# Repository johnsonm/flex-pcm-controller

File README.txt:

This is a low-current low-DC-voltage 2.5cm by 5cm PCM controller based
on a 555 timer.  It is built in KiCad.  The license, which applies to
all unique content (not inherited components) is in the LICENSE.txt
file.  Instructions for some potential modifications and use are in
the schematic.

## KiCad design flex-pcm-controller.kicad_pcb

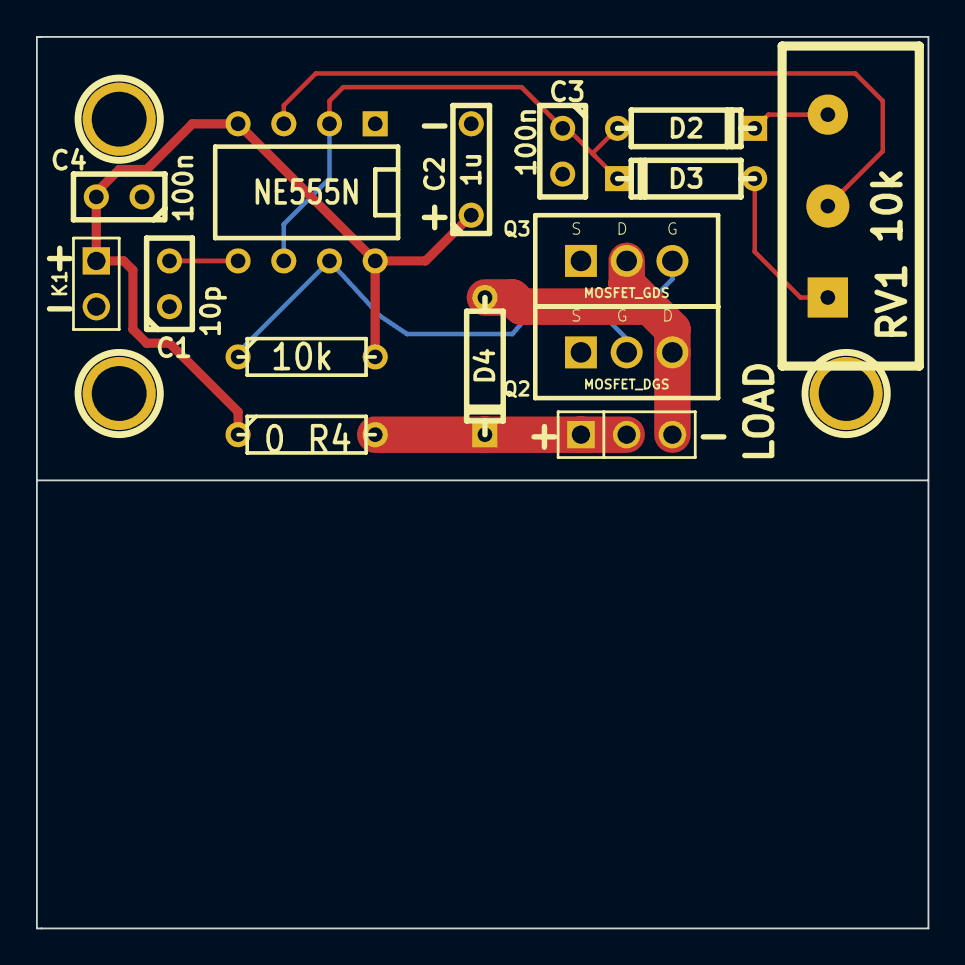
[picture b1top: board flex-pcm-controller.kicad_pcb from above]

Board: 2 copper layers, 49.5 x 49.5 mm, 18 parts (0 on the bottom side), 10 nets.

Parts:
1PIN, 1PIN#2, 1PIN#3: P***; 1pin
C1: 10p; C1
C2: 1u; C2
C3, C4: 100n; C1
D2, D3, D4: DIODESCH; D3
K1: POWER; PIN_ARRAY_2X1
K2: LOAD; PIN_ARRAY_3X1
Q2: MOSFET_DGS; TO220DGS
Q3: MOSFET_GDS; TO220GDS
R2: 10k; R3
R4: 0; R3
RV1: 10k; POTA_Fav
U1: NE555N; DIP-8__300

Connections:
/SIG: Q2.G, Q3.G, R2.1, U1.7
/Vload+: D4.2, K2.1, K2.2, R4.2
/Vload-: D4.1, K2.3, Q2.D, Q3.D
GND: C1.1, C2.2, C3.2, C4.1, K1.2, Q2.S, Q3.S, U1.1
unnamed: D2.2, RV1.3
unnamed: RV1.2, U1.3
unnamed: D3.1, RV1.1
unnamed: C1.2, U1.5
unnamed: C3.1, D2.1, D3.2, U1.2, U1.6
VCC: C2.1, C4.2, K1.1, R2.2, R4.1, U1.4, U1.8

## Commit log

2014-09-16 Initial version of flexible 555-based PCM controller
2014-09-17 Remove PNP option, lay out to take half of a 5cm^2 board
2014-09-17 Panelize 2up on 5x5cm board with perf
2014-09-18 Electrolytic footprint, rearrange schematic
    Switch C2 footprint to be an electrolytic rather than film capacitor.
    Rearrange schematic to be more logical after removing PNP.
    Add PDF and SVG plots of schematic.
2014-09-18 revert MOSFET descriptions to DGS/GDS footprint designations
2014-09-18 Add GND to LOAD connector for Vsupply+ == Vcc
2014-09-19 Change internal cuts to mechanical holes; turn MOSFETs back-to-back
    Replaced the internal cuts with NPTH mechanical holes for the
    panelized snap line.
    Swapped the MOSFET locations and rotated one so that they are now
    back-to-back with the heat sink toward the middle to leave more
    options for the K2 LOAD connector. This should allow wires,
    headers, or 0.1" pitch screw connector terminal block connectors.
2014-09-24 remove silkscreen line on RV1 crossing screw hole
2014-09-28 move VCC trace away from mounting hole
2014-09-28 remove acute angle from SIG trace to GDS MOSFET
2014-10-04 add option for .1 pitch potentiometer
2014-10-05 move power components toward center to accomodate additional connector style; comment in schematic about potentiometer styles and connector current ratings; add gerber files
2014-10-05 re-route Vcc under 555 chip
2014-10-06 replace R4 jumper with 780x voltage regulator; add its required C5 330nF capacitor
2014-10-06 Replace mutually exclusive MOSFETs with single MOSFET
    Previously, there were two MOSFETs in the schematic, one for each pin
    configuration, to make it easy to place two components on the board.
    These have been replaced by a single MOSFET and an edited modules with
    two sets of pins, one for each of the GDS and DGS pinouts.
2014-10-23 first changes from first proto boards
    - Larger holes for 0.2 pitch potentiometer
    - Larger holes for 4-connector
    - Renamed 7805 to 78xx with clarified instructions
    - Move MOSFET_N GDS designation away from 4-connector
    - Move +/- indication to be more visible around 4-connector
2014-12-10 remove npth depanelization perf
2015-03-07 Update rendered schematics, add LICENSE and README
